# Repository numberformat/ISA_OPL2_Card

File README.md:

# README

ISA OPL2 Card is a sound card based on Yamaha OPL2 chip, officially known as YM3812. This card is compatible with the AdLib Music Synthesizer Card that was very popular in late 80's - early
90's.

This card is based on a [design from Sergey Kiselev](http://www.malinov.com/Home/sergeys-projects/isa-opl2-card) with the modifications listed in the Revisions Section below.

## Revisions

NOAMi r1
- Added additional footprint for a more commonly available RK097N potentiometer
- Made connector pads shorter since half of them were not making contact with the connector pins.

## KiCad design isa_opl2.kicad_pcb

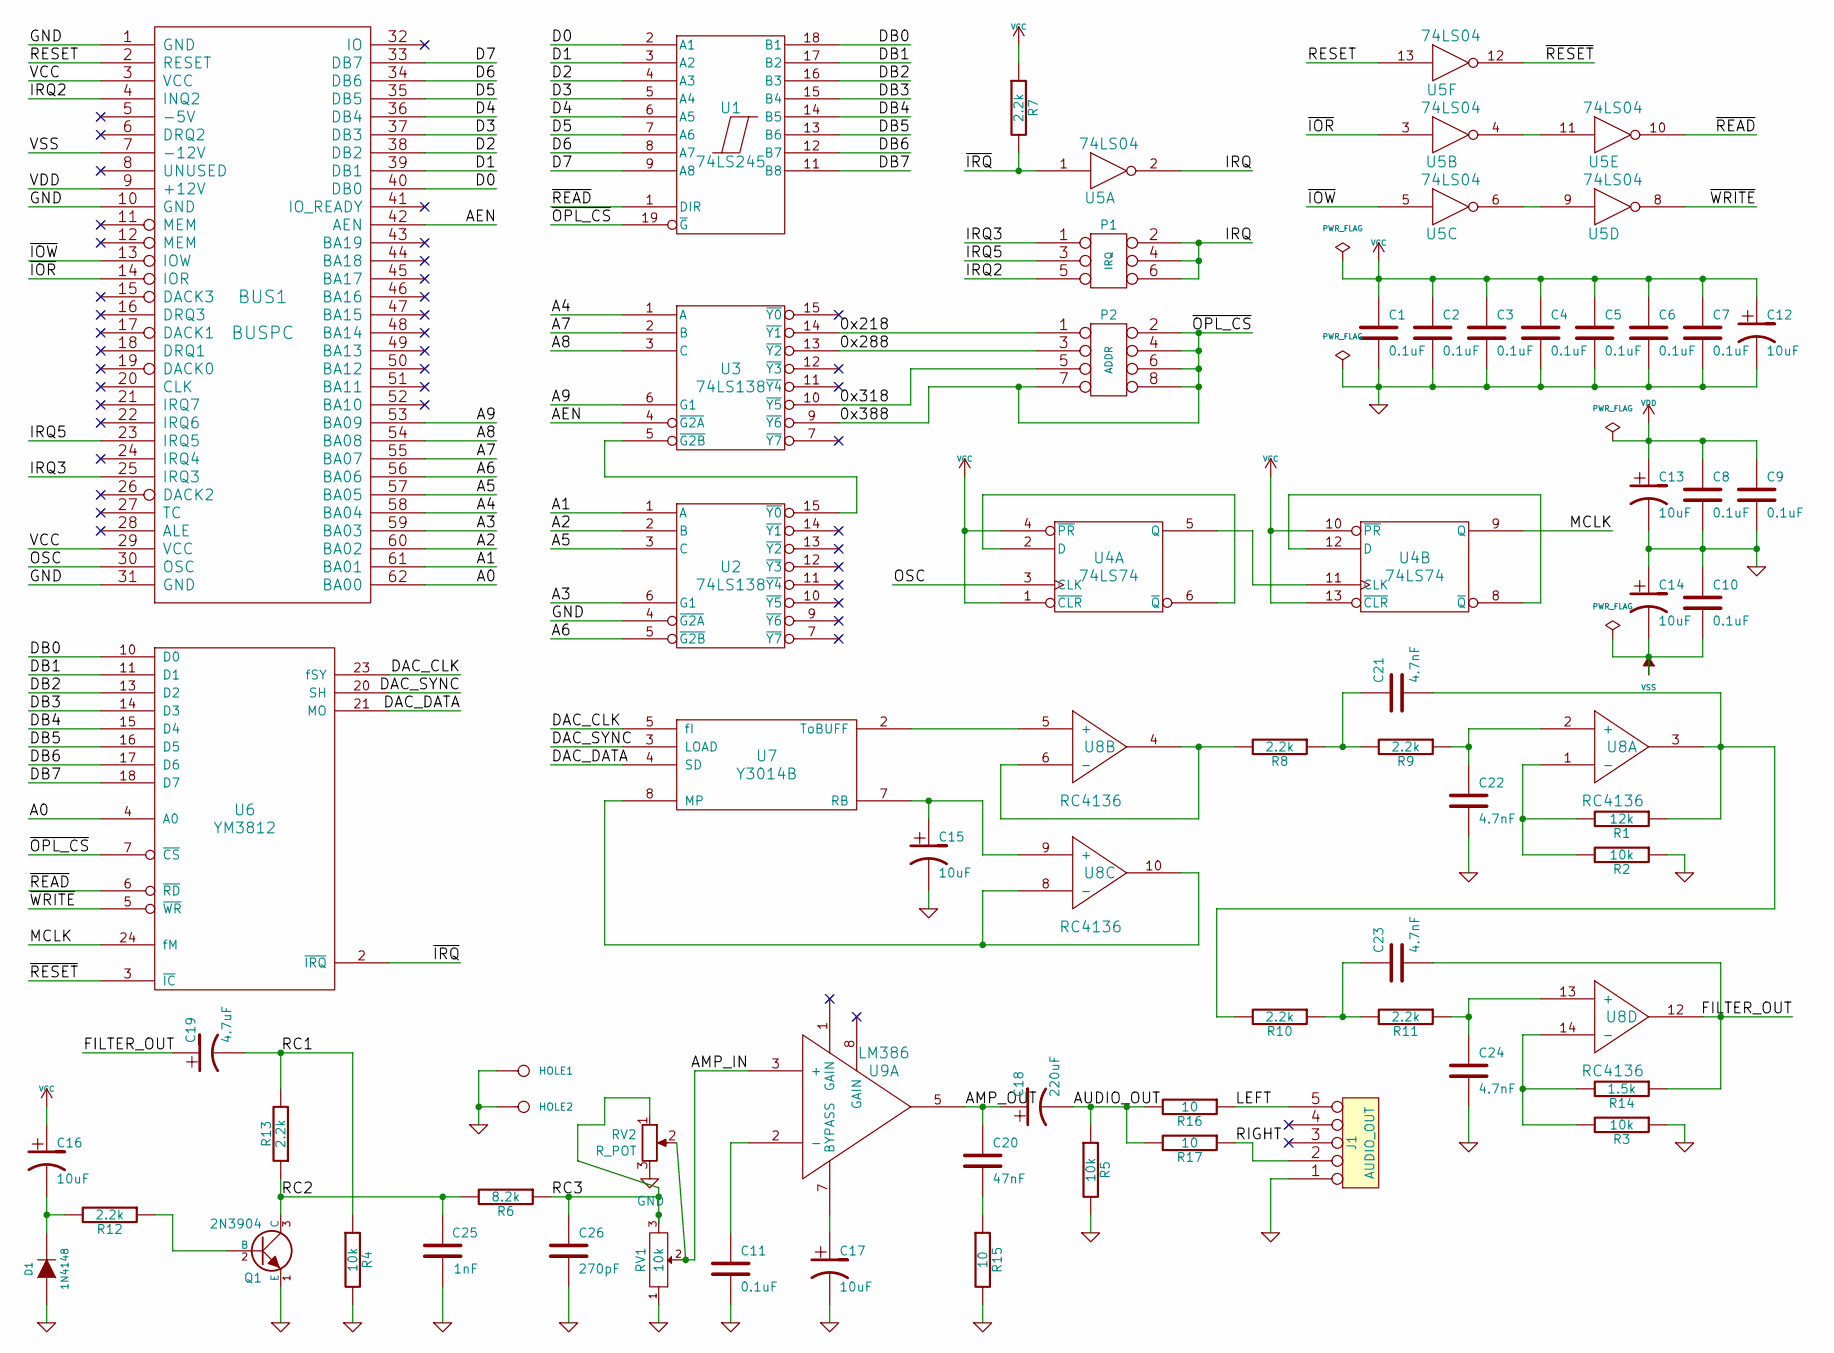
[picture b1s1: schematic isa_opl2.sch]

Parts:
BUS1: BUSPC
C1, C2, C3, C4, C5, C6, C7, C8, C9, C10, C11: 0.1uF
C12, C13, C14, C15, C16, C17: 10uF
C18: 220uF
C19: 4.7uF
C20: 47nF
C21, C22, C23, C24: 4.7nF
C25: 1nF
C26: 270pF
D1: 1N4148
HOLE1, HOLE2: CONN_1
J1: AUDIO_OUT
P1: IRQ
P2: ADDR
Q1: 2N3904
R1: 12k
R2, R3, R4, R5: 10k
R6: 8.2k
R7, R8, R9, R10, R11, R12, R13: 2.2k
R14: 1.5k
R15, R16, R17: 10
RV1: 10k
RV2: R_POT; Potentiometer_Vishay_T73XW_Horizontal
U1: 74LS245
U2, U3: 74LS138
U4: 74LS74
U5: 74LS04
U6: YM3812
U7: Y3014B
U8: RC4136
U9: LM386

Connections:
/0x218: P2.1, U3.14 (~Y1)
/0x288: P2.3, U3.13 (~Y2)
/0x318: P2.5, U3.10 (~Y5)
/0x388: P2.2, P2.4, P2.6, P2.7, P2.8, U1.19 (~G), U3.9 (~Y6), U6.7 (~CS)
/A0: BUS1.62 (BA00), U6.4 (A0)
/A1: BUS1.61 (BA01), U2.1 (A)
/A2: BUS1.60 (BA02), U2.2 (B)
/A3: BUS1.59 (BA03), U2.6 (G1)
/A4: BUS1.58 (BA04), U3.1 (A)
/A5: BUS1.57 (BA05), U2.3 (C)
/A6: BUS1.56 (BA06), U2.5 (~G2B)
/A7: BUS1.55 (BA07), U3.2 (B)
/A8: BUS1.54 (BA08), U3.3 (C)
/A9: BUS1.53 (BA09), U3.6 (G1)
/AEN: BUS1.42 (AEN), U3.4 (~G2A)
/AMP_IN: RV1.2, RV2.2, U9.3 (+)
/AMP_OUT: C18.1, C20.1, U9.5
/AUDIO_OUT: C18.2, R5.1, R16.2, R17.2
/D0: BUS1.40 (DB0), U1.2 (A1)
/D1: BUS1.39 (DB1), U1.3 (A2)
/D2: BUS1.38 (DB2), U1.4 (A3)
/D3: BUS1.37 (DB3), U1.5 (A4)
/D4: BUS1.36 (DB4), U1.6 (A5)
/D5: BUS1.35 (DB5), U1.7 (A6)
/D6: BUS1.34 (DB6), U1.8 (A7)
/D7: BUS1.33 (DB7), U1.9 (A8)
/DAC_CLK: U6.23 (fSY), U7.5 (fI)
/DAC_DATA: U6.21 (MO), U7.4 (SD)
/DAC_SYNC: U6.20 (SH), U7.3 (LOAD)
/DB0: U1.18 (B1), U6.10 (D0)
/DB1: U1.17 (B2), U6.11 (D1)
/DB2: U1.16 (B3), U6.13 (D2)
/DB3: U1.15 (B4), U6.14 (D3)
/DB4: U1.14 (B5), U6.15 (D4)
/DB5: U1.13 (B6), U6.16 (D5)
/DB6: U1.12 (B7), U6.17 (D6)
/DB7: U1.11 (B8), U6.18 (D7)
/FILTER_OUT: C19.1, C23.2, R14.1, U8.12
/IRQ: P1.2, P1.4, P1.6, U5.2
/IRQ2: BUS1.4 (INQ2), P1.5
/IRQ3: BUS1.25 (IRQ3), P1.1
/IRQ5: BUS1.23 (IRQ5), P1.3
/LEFT: J1.5, R16.1
/MCLK: U4.9 (Q), U6.24 (fM)
/OSC: BUS1.30 (OSC), U4.3 (CLK)
/RC1: C19.2, R4.1, R13.2
/RC2: C25.2, Q1.3 (C), R6.2, R13.1
/RC3: C26.1, R6.1, RV1.3, RV2.1
/RESET: BUS1.2 (RESET), U5.13
/RIGHT: J1.2, R17.1
/~IOR: BUS1.14 (IOR), U5.3
/~IOW: BUS1.13 (IOW), U5.5
/~IRQ: R7.2, U5.1, U6.2 (~IRQ)
/~READ: U1.1 (DIR), U5.10, U6.6 (~RD)
/~RESET: U5.12, U6.3 (~IC)
/~WRITE: U5.8, U6.5 (~WR)
GND: BUS1.1 (GND), BUS1.10 (GND), BUS1.31 (GND), C1.2, C2.2, C3.2, C4.2, C5.2, C6.2, C7.2, C8.2, C9.2, C10.1, C11.2, C12.2, C13.2, C14.1, C15.2, C17.2, C22.2, C24.2, C25.1, C26.2, D1.1 (A), HOLE1.1, HOLE2.1, J1.1, Q1.1 (E), R2.1, R3.1, R4.2, R5.2, R15.2, RV1.1, RV2.3, U1.10 (GND), U2.4 (~G2A), U2.8 (GND), U3.8 (GND), U4.7 (GND), U5.7 (GND), U6.12 (GND), U7.6 (GND), U9.4 (GND)
unnamed: C11.1, U9.2 (-)
unnamed: C15.1, U7.7 (RB), U8.9 (+)
unnamed: C16.2, D1.2 (K), R12.2
unnamed: C17.1, U9.7 (BYPASS)
unnamed: C20.2, R15.1
unnamed: C21.1, R8.1, R9.2
unnamed: C21.2, R1.1, R10.2, U8.3
unnamed: C22.1, R9.1, U8.2 (+)
unnamed: C23.1, R10.1, R11.2
unnamed: C24.1, R11.1, U8.13 (+)
unnamed: Q1.2 (B), R12.1
unnamed: R1.2, R2.2, U8.1 (-)
unnamed: R8.2, U8.4, U8.6 (-)
unnamed: R3.2, R14.2, U8.14 (-)
unnamed: U2.15 (~Y0), U3.5 (~G2B)
unnamed: U4.2 (D), U4.6 (~Q)
unnamed: U4.5 (Q), U4.11 (CLK)
unnamed: U4.8 (~Q), U4.12 (D)
unnamed: U5.6, U5.9
unnamed: U5.4, U5.11
unnamed: U7.2 (ToBUFF), U8.5 (+)
unnamed: U7.8 (MP), U8.8 (-), U8.10
VCC: BUS1.3 (VCC), BUS1.29 (VCC), C1.1, C2.1, C3.1, C4.1, C5.1, C6.1, C7.1, C12.1, C16.1, R7.1, U1.20 (VCC), U2.16 (VCC), U3.16 (VCC), U4.1 (~CLR), U4.4 (~PR), U4.10 (~PR), U4.13 (~CLR), U4.14 (VCC), U5.14 (VCC), U6.1 (VCC), U7.1 (VCC)
VDD: BUS1.9 (+12V), C8.1, C9.1, C13.1, U8.11 (VDD), U9.6 (VDD)
VSS: BUS1.7 (-12V), C10.2, C14.2, U8.7 (VSS)

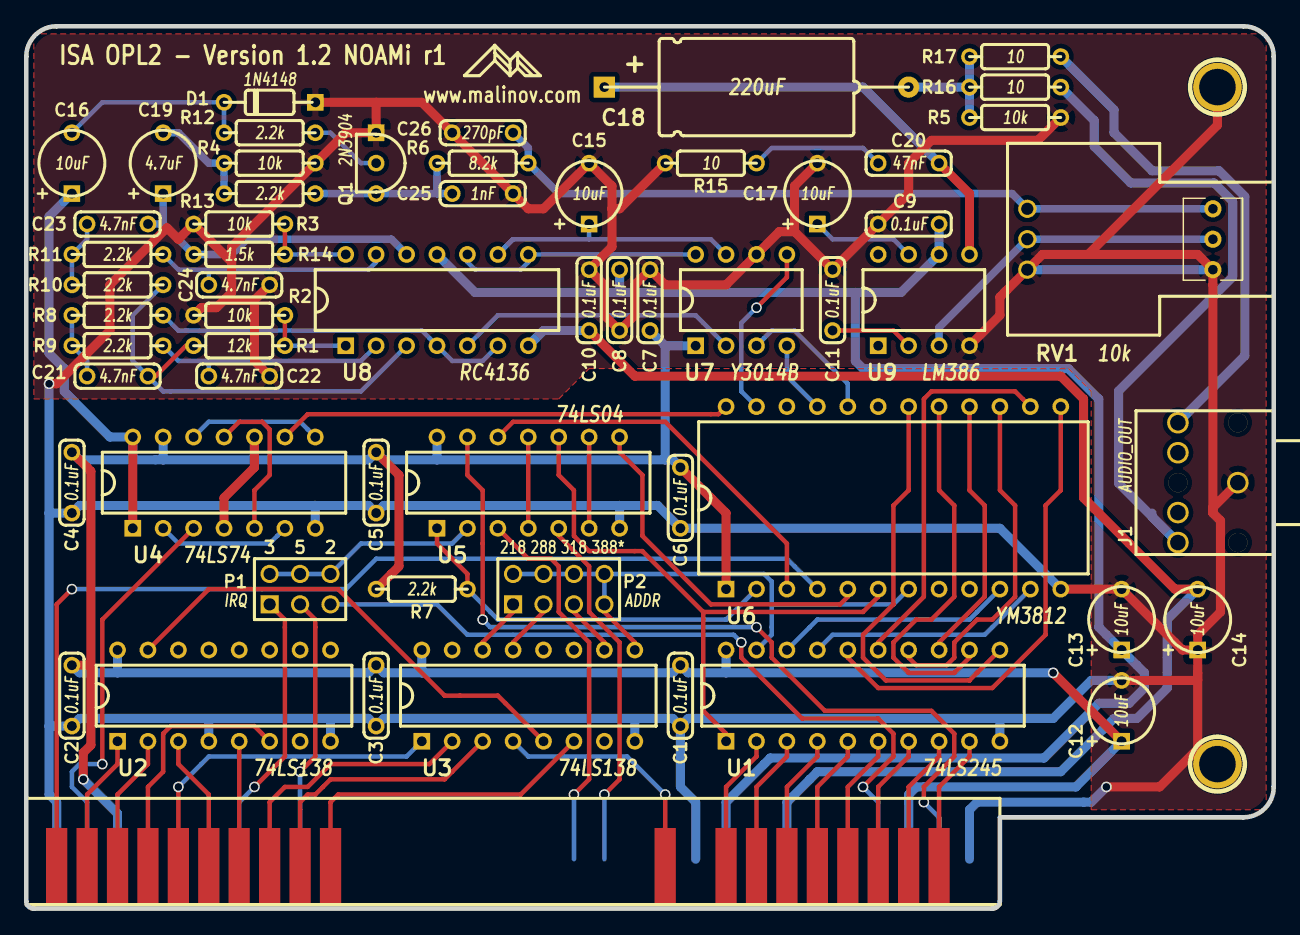
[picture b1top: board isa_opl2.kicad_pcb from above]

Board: 2 copper layers, 104.1 x 73.7 mm, 61 parts (0 on the bottom side), 82 nets.

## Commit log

2021-11-06 NOAMi r1 - added additional footprint for cheaper pot and more clearence for 45 deg chamfer
2021-11-24 Made connector pads shorter since half of them were not making contact with the connector pins
2022-04-10 new project files
2022-04-19 Added service/support info
